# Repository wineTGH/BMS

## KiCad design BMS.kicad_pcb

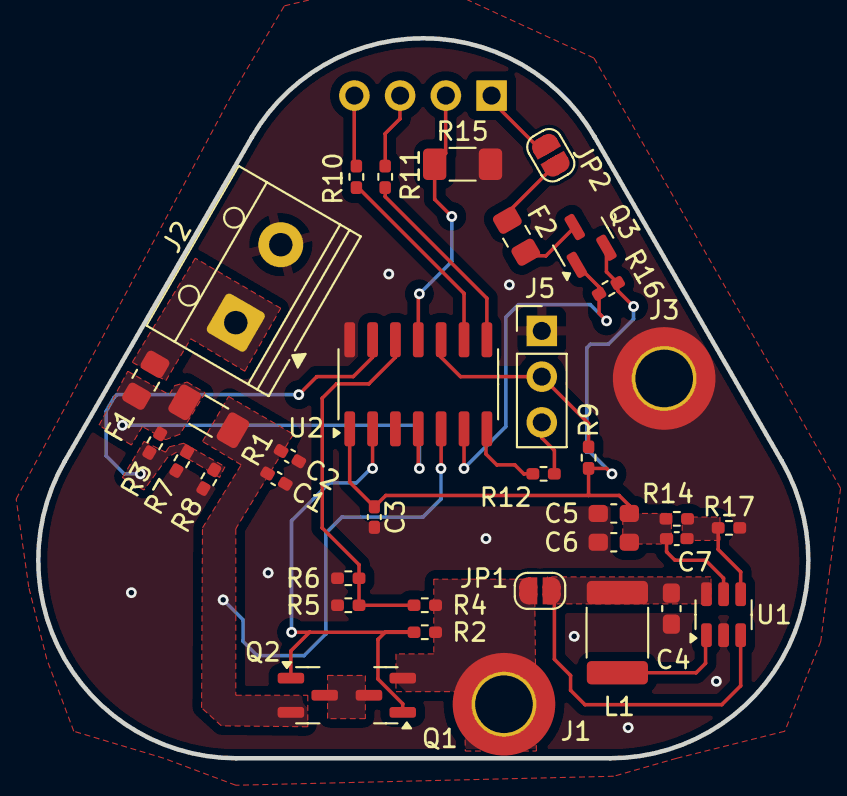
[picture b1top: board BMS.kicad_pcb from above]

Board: 2 copper layers, 42.8 x 40.0 mm, 38 parts (1 on the bottom side), 25 nets.

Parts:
C1, C2, C3: 100n; C_0402_1005Metric_Pad0.74x0.62mm_HandSolder
C4, C5, C6: 10u; C_0603_1608Metric_Pad1.08x0.95mm_HandSolder
C7: 270p; C_0402_1005Metric_Pad0.74x0.62mm_HandSolder
F1, F2: BSMD0805-110-6V; Fuse_0805_2012Metric_Pad1.15x1.40mm_HandSolder
J1: BATT+; MountingHole_3.2mm_M3_ISO7380_Pad_TopOnly
J2: LOAD; TerminalBlock_RND_205-00012_1x02_P5.00mm_Horizontal
J3: BATT-; MountingHole_3.2mm_M3_ISO7380_Pad_TopOnly
J4: QWIIC; PinHeader_1x04_P2.54mm_Vertical
J5: PROG; PinHeader_1x03_P2.54mm_Vertical
JP1: MCU_VCC; SolderJumper-2_P1.3mm_Open_RoundedPad1.0x1.5mm
JP2: I2C_V; SolderJumper-2_P1.3mm_Open_RoundedPad1.0x1.5mm
L1: 2.2uH; L_1812_4532Metric_Pad1.30x3.40mm_HandSolder
Q1, Q2, Q3: SI2333; SOT-23
R1, R15: 0.1R; R_1206_3216Metric_Pad1.30x1.75mm_HandSolder
R2, R3, R4, R5, R6, R7, R8, R16: 1M; R_0402_1005Metric_Pad0.72x0.64mm_HandSolder
R9, R17: 100k; R_0402_1005Metric_Pad0.72x0.64mm_HandSolder
R10, R11, R12: 120R; R_0402_1005Metric_Pad0.72x0.64mm_HandSolder
R14: 560k; R_0402_1005Metric_Pad0.72x0.64mm_HandSolder
U1: TLV61070ADBV; SOT-23-6
U2: ATtiny824-SSU; SOIC-14_3.9x8.7mm_P1.27mm

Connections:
3V3CUTOFF: Q3.1 (G), R16.2, U2.6 (RXD)
+BATT: J1.1, JP1.1 (A), Q1.2 (S), R2.1, R4.1
ADC_BATT: R4.2, R5.1, R6.1, U2.12 (AIN2)
ADC_LN: F1.1, R1.2, R3.1, U2.4 (AIN6)
ADC_LOAD: R3.2, R7.1, R8.1, U2.13 (AIN3)
ADC_LP: C1.1, C2.1, Q2.2 (S), R1.1, U2.5 (AIN7)
ADC_SP: J4.2, R15.1, U2.11 (PA1)
CUTOFF: Q1.1 (G), Q2.1 (G), R2.2, U2.2 (PA4)
GND: C1.2, C2.2, C3.2, C4.2, C5.2, C6.2, J2.2, J3.1, J5.1, R5.2, R6.2, R7.2, R8.2, R15.2, R17.2, U1.2 (GND), U2.14 (GND)
unnamed: F1.2, J2.1
unnamed: J4.1, JP2.1 (A)
unnamed: J4.3, R11.1
unnamed: J4.4, R10.1
unnamed: C4.1, JP1.2 (B), L1.1, U1.3 (EN), U1.6 (V_{IN})
unnamed: F2.1, JP2.2 (B)
unnamed: Q1.3 (D), Q2.3 (D)
unnamed: F2.2, Q3.3 (D)
unnamed: L1.2, U1.1 (SW)
unnamed: C7.1, R14.2, R17.1, U1.4 (V_{FB})
unnamed: R12.2, U2.7 (TXD)
SCL: R10.2, U2.9 (SCL)
SDA: R11.2, U2.8 (SDA)
TXD: J5.3, R12.1
UPDI: J5.2, R9.2, U2.10 (~RESET/PA0)
VCC: C3.1, C5.1, C6.1, C7.2, Q3.2 (S), R9.1, R14.1, R16.1, U1.5 (V_{OUT}), U2.1 (VCC)

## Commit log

2025-09-26 Finished schematic
2025-11-25 First PCB design
2025-11-25 Final(-ish) PCB
